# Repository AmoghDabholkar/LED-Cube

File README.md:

# LED-Cube
In this project, we made a 10x10x10 LEDs (2 meters x 2 meters x 2 meters) LED Cube. A LED cube is a visual treat with 3D effects and patterns. It works on the concept of Persistence of Vision.

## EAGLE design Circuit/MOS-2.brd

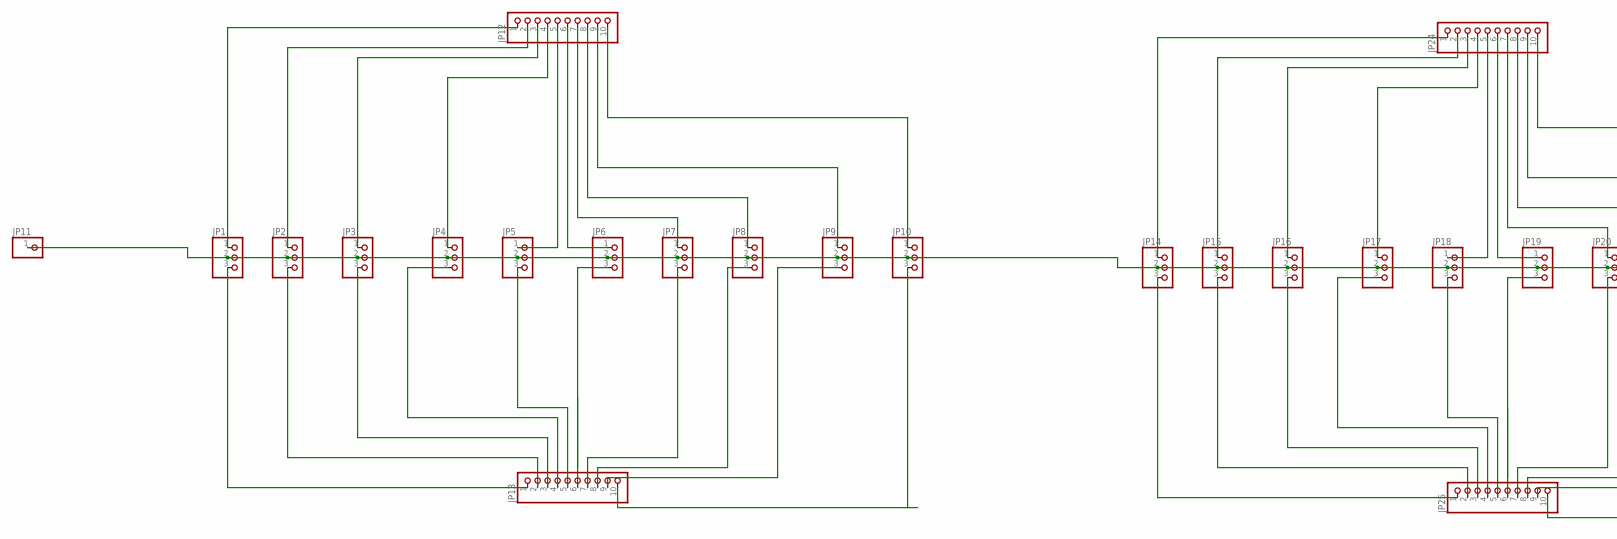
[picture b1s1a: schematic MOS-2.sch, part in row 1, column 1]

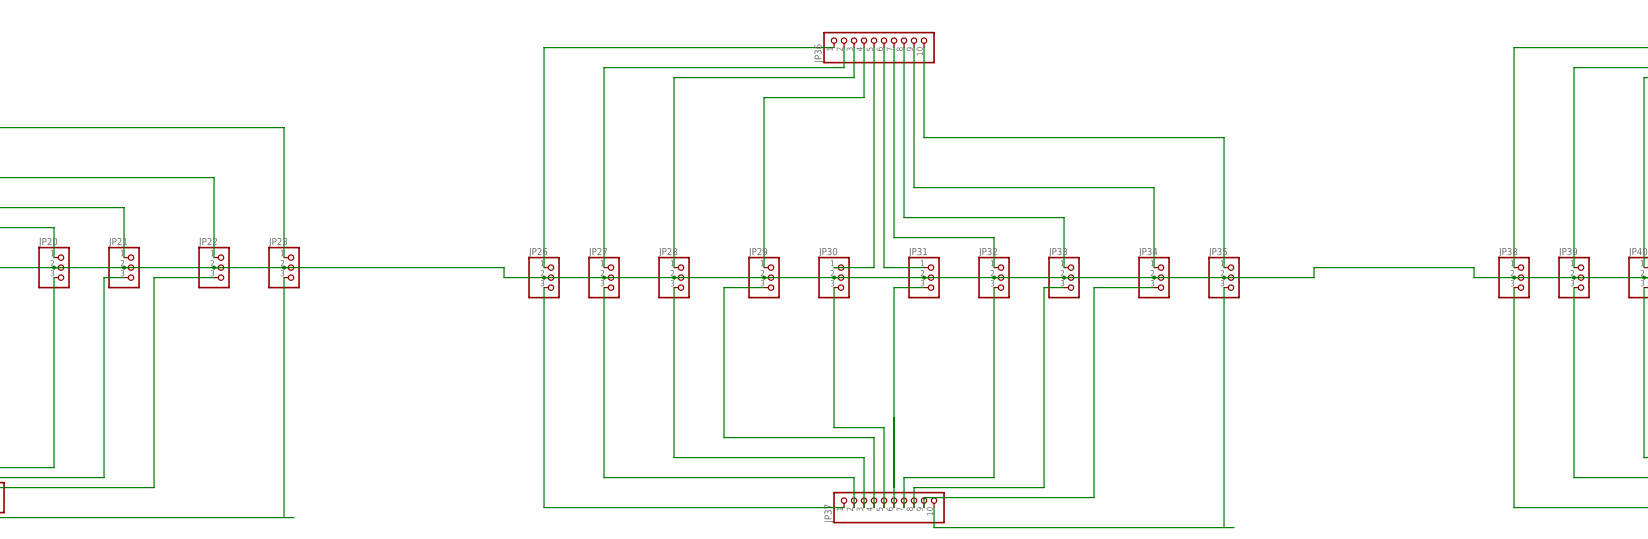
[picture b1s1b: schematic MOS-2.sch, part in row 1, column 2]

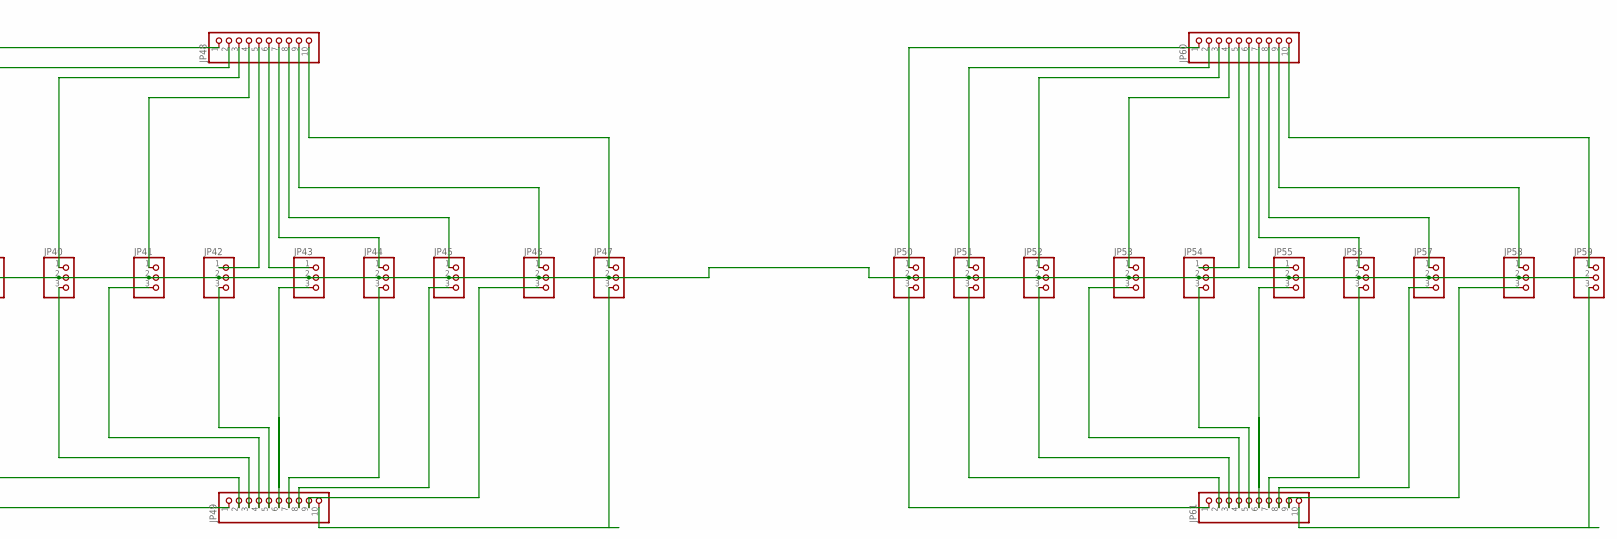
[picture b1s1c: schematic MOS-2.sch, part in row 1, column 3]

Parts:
JP1, JP2, JP3, JP4, JP5, JP6, JP7, JP8, JP9, JP10, JP14, JP15, JP16, JP17, JP18, JP19, JP20, JP21, JP22, JP23, JP26, JP27, JP28, JP29, JP30, JP31, JP32, JP33, JP34, JP35, JP38, JP39, JP40, JP41, JP42, JP43, JP44, JP45, JP46, JP47, JP50, JP51, JP52, JP53, JP54, JP55, JP56, JP57, JP58, JP59: PINHD-1X3; 1X03
JP11: PINHD-1X1; 1X01
JP12, JP13, JP24, JP25, JP36, JP37, JP48, JP49, JP60, JP61: PINHD-1X10; 1X10

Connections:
unnamed: JP1.2, JP2.2, JP3.2, JP4.2, JP5.2, JP6.2, JP7.2, JP8.2, JP9.2, JP10.2, JP11.1, JP14.2, JP15.2, JP16.2, JP17.2, JP18.2, JP19.2, JP20.2, JP21.2, JP22.2, JP23.2, JP26.2, JP27.2, JP28.2, JP29.2, JP30.2, JP31.2, JP32.2, JP33.2, JP34.2, JP35.2, JP38.2, JP39.2, JP40.2, JP41.2, JP42.2, JP43.2, JP44.2, JP45.2, JP46.2, JP47.2, JP50.2, JP51.2, JP52.2, JP53.2, JP54.2, JP55.2, JP56.2, JP57.2, JP58.2, JP59.2
unnamed: JP1.1, JP12.1
unnamed: JP2.1, JP12.2
unnamed: JP3.1, JP12.3
unnamed: JP4.1, JP12.4
unnamed: JP5.1, JP12.5
unnamed: JP6.1, JP12.6
unnamed: JP7.1, JP12.7
unnamed: JP8.1, JP12.8
unnamed: JP9.1, JP12.9
unnamed: JP10.1, JP12.10
unnamed: JP1.3, JP13.1
unnamed: JP2.3, JP13.2
unnamed: JP3.3, JP13.3
unnamed: JP5.3, JP13.5
unnamed: JP10.3, JP13.10
unnamed: JP9.3, JP13.9
unnamed: JP8.3, JP13.8
unnamed: JP7.3, JP13.7
unnamed: JP6.3, JP13.6
unnamed: JP14.1, JP24.1
unnamed: JP4.3, JP13.4
unnamed: JP15.1, JP24.2
unnamed: JP16.1, JP24.3
unnamed: JP17.1, JP24.4
unnamed: JP18.1, JP24.5
unnamed: JP19.1, JP24.6
unnamed: JP20.1, JP24.7
unnamed: JP21.1, JP24.8
unnamed: JP22.1, JP24.9
unnamed: JP23.1, JP24.10
unnamed: JP14.3, JP25.1
unnamed: JP15.3, JP25.2
unnamed: JP16.3, JP25.3
unnamed: JP18.3, JP25.5
unnamed: JP23.3, JP25.10
unnamed: JP22.3, JP25.9
unnamed: JP21.3, JP25.8
unnamed: JP20.3, JP25.7
unnamed: JP19.3, JP25.6
unnamed: JP17.3, JP25.4
unnamed: JP26.1, JP36.1
unnamed: JP27.1, JP36.2
unnamed: JP28.1, JP36.3
unnamed: JP29.1, JP36.4
unnamed: JP30.1, JP36.5
unnamed: JP31.1, JP36.6
unnamed: JP32.1, JP36.7
unnamed: JP33.1, JP36.8
unnamed: JP34.1, JP36.9
unnamed: JP35.1, JP36.10
unnamed: JP26.3, JP37.1
unnamed: JP27.3, JP37.2
unnamed: JP28.3, JP37.3
unnamed: JP30.3, JP37.5
unnamed: JP35.3, JP37.10
unnamed: JP34.3, JP37.9
unnamed: JP33.3, JP37.8
unnamed: JP32.3, JP37.7
unnamed: JP31.3, JP37.6
unnamed: JP29.3, JP37.4
unnamed: JP38.1, JP48.1
unnamed: JP39.1, JP48.2
unnamed: JP40.1, JP48.3
unnamed: JP41.1, JP48.4
unnamed: JP42.1, JP48.5
unnamed: JP43.1, JP48.6
unnamed: JP44.1, JP48.7
unnamed: JP45.1, JP48.8
unnamed: JP46.1, JP48.9
unnamed: JP47.1, JP48.10
unnamed: JP38.3, JP49.1
unnamed: JP39.3, JP49.2
unnamed: JP40.3, JP49.3
unnamed: JP42.3, JP49.5
unnamed: JP47.3, JP49.10
unnamed: JP46.3, JP49.9
unnamed: JP45.3, JP49.8
unnamed: JP44.3, JP49.7
unnamed: JP43.3, JP49.6
unnamed: JP41.3, JP49.4
unnamed: JP50.1, JP60.1
unnamed: JP51.1, JP60.2
unnamed: JP52.1, JP60.3
unnamed: JP53.1, JP60.4
unnamed: JP54.1, JP60.5
unnamed: JP55.1, JP60.6
unnamed: JP56.1, JP60.7
unnamed: JP57.1, JP60.8
unnamed: JP58.1, JP60.9
unnamed: JP59.1, JP60.10
unnamed: JP50.3, JP61.1
unnamed: JP51.3, JP61.2
unnamed: JP52.3, JP61.3
unnamed: JP54.3, JP61.5
unnamed: JP59.3, JP61.10
unnamed: JP58.3, JP61.9
unnamed: JP57.3, JP61.8
unnamed: JP56.3, JP61.7
unnamed: JP55.3, JP61.6
unnamed: JP53.3, JP61.4

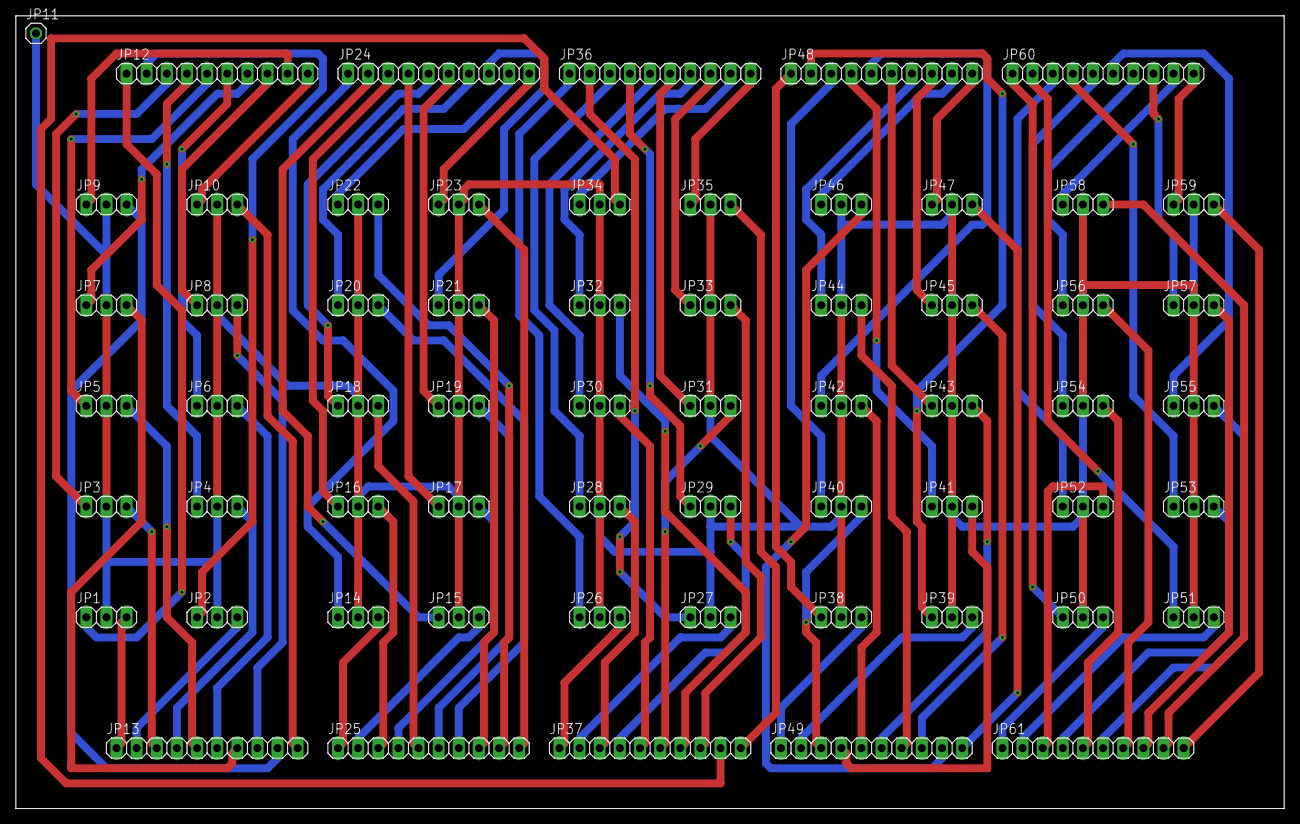
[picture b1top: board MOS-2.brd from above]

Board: 2 copper layers, 160.0 x 100.0 mm, 61 parts (0 on the bottom side), 101 nets.

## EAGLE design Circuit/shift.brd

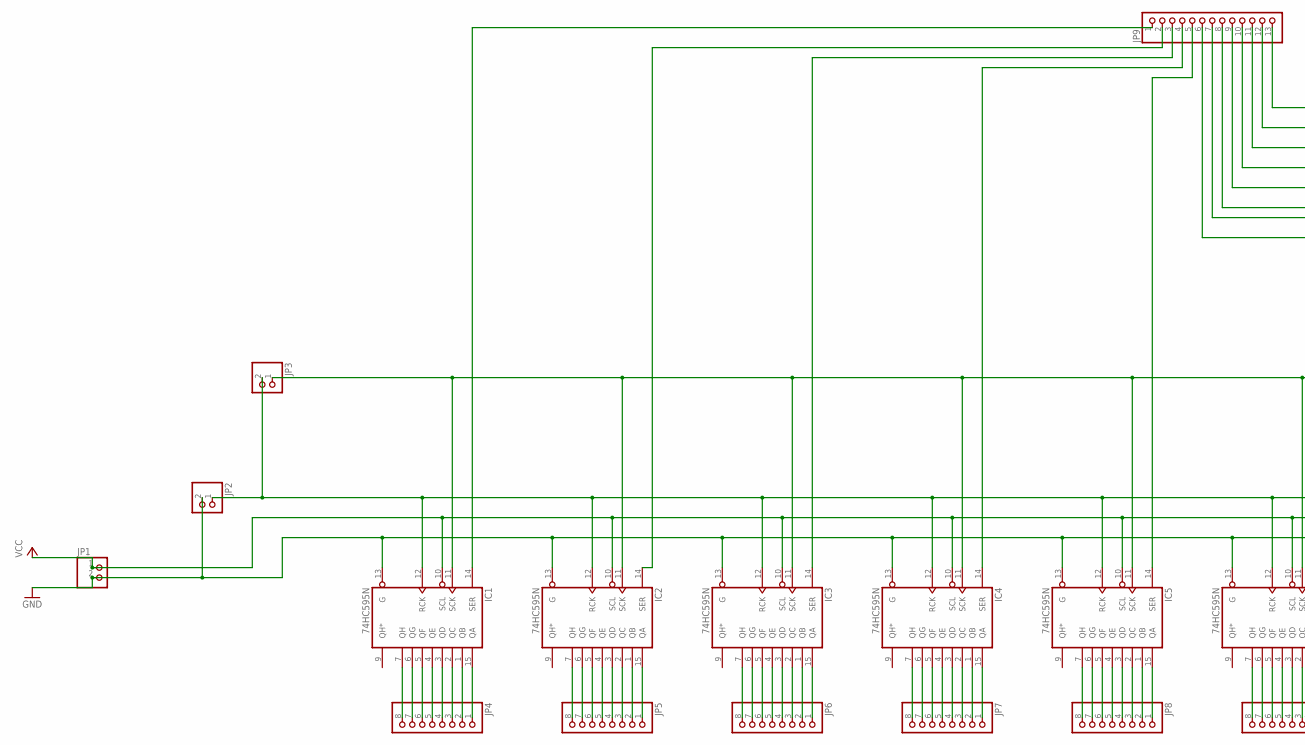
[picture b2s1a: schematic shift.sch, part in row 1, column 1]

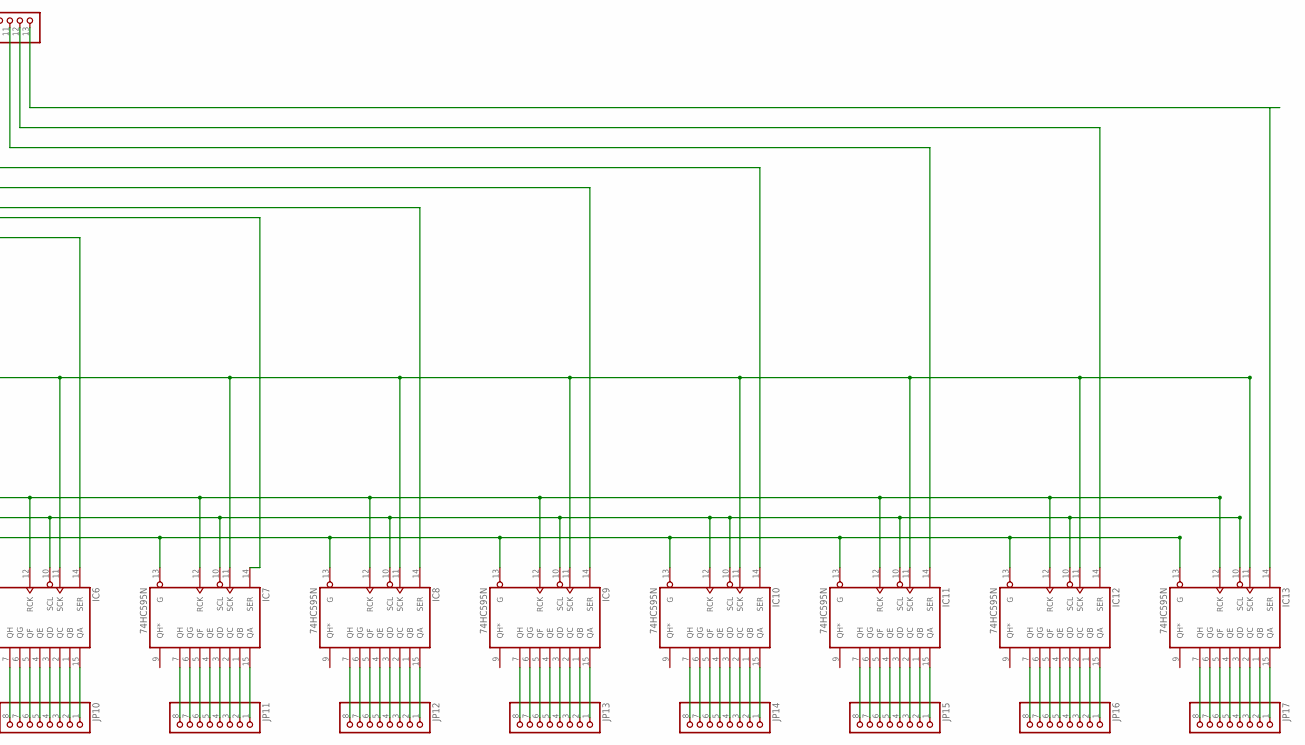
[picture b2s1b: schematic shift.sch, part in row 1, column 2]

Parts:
IC1, IC2, IC3, IC4, IC5, IC6, IC7, IC8, IC9, IC10, IC11, IC12, IC13: 74HC595N; DIL16
JP1, JP2, JP3: PINHD-1X2; 1X02
JP4, JP5, JP6, JP7, JP8, JP10, JP11, JP12, JP13, JP14, JP15, JP16, JP17: PINHD-1X8; 1X08
JP9: PINHD-1X13; 1X13

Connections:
GND: IC1.8 (GND), IC1.13 (G), IC2.8 (GND), IC2.13 (G), IC3.8 (GND), IC3.13 (G), IC4.8 (GND), IC4.13 (G), IC5.8 (GND), IC5.13 (G), IC6.8 (GND), IC6.13 (G), IC7.8 (GND), IC7.13 (G), IC8.8 (GND), IC8.13 (G), IC9.8 (GND), IC9.13 (G), IC10.8 (GND), IC10.13 (G), IC11.8 (GND), IC11.13 (G), IC12.8 (GND), IC12.13 (G), IC13.8 (GND), IC13.13 (G), JP1.2, JP2.2
unnamed: IC1.7 (QH), JP4.8
unnamed: IC1.6 (QG), JP4.7
unnamed: IC1.5 (QF), JP4.6
unnamed: IC1.4 (QE), JP4.5
unnamed: IC1.3 (QD), JP4.4
unnamed: IC1.2 (QC), JP4.3
unnamed: IC1.1 (QB), JP4.2
unnamed: IC1.15 (QA), JP4.1
unnamed: IC1.11 (SCK), IC2.11 (SCK), IC3.11 (SCK), IC4.11 (SCK), IC5.11 (SCK), IC6.11 (SCK), IC7.11 (SCK), IC8.11 (SCK), IC9.11 (SCK), IC10.11 (SCK), IC11.11 (SCK), IC12.11 (SCK), IC13.11 (SCK), JP3.1
unnamed: IC1.14 (SER), JP9.1
unnamed: IC2.14 (SER), JP9.2
unnamed: IC2.7 (QH), JP5.8
unnamed: IC2.6 (QG), JP5.7
unnamed: IC2.5 (QF), JP5.6
unnamed: IC2.4 (QE), JP5.5
unnamed: IC2.3 (QD), JP5.4
unnamed: IC2.2 (QC), JP5.3
unnamed: IC2.1 (QB), JP5.2
unnamed: IC2.15 (QA), JP5.1
unnamed: IC3.14 (SER), JP9.3
unnamed: IC4.14 (SER), JP9.4
unnamed: IC3.7 (QH), JP6.8
unnamed: IC3.6 (QG), JP6.7
unnamed: IC3.5 (QF), JP6.6
unnamed: IC3.4 (QE), JP6.5
unnamed: IC3.3 (QD), JP6.4
unnamed: IC3.2 (QC), JP6.3
unnamed: IC3.1 (QB), JP6.2
unnamed: IC3.15 (QA), JP6.1
unnamed: IC5.14 (SER), JP9.5
unnamed: IC6.7 (QH), JP10.8
unnamed: IC4.7 (QH), JP7.8
unnamed: IC4.6 (QG), JP7.7
unnamed: IC4.5 (QF), JP7.6
unnamed: IC4.4 (QE), JP7.5
unnamed: IC4.3 (QD), JP7.4
unnamed: IC4.2 (QC), JP7.3
unnamed: IC4.1 (QB), JP7.2
unnamed: IC4.15 (QA), JP7.1
unnamed: IC6.6 (QG), JP10.7
unnamed: IC6.5 (QF), JP10.6
unnamed: IC5.7 (QH), JP8.8
unnamed: IC5.6 (QG), JP8.7
unnamed: IC5.5 (QF), JP8.6
unnamed: IC5.4 (QE), JP8.5
unnamed: IC5.3 (QD), JP8.4
unnamed: IC5.2 (QC), JP8.3
unnamed: IC5.1 (QB), JP8.2
unnamed: IC5.15 (QA), JP8.1
unnamed: IC6.4 (QE), JP10.5
unnamed: IC6.3 (QD), JP10.4
unnamed: IC6.2 (QC), JP10.3
unnamed: IC6.1 (QB), JP10.2
unnamed: IC6.15 (QA), JP10.1
unnamed: IC7.7 (QH), JP11.8
unnamed: IC7.6 (QG), JP11.7
unnamed: IC7.5 (QF), JP11.6
unnamed: IC7.4 (QE), JP11.5
unnamed: IC7.3 (QD), JP11.4
unnamed: IC7.2 (QC), JP11.3
unnamed: IC7.1 (QB), JP11.2
unnamed: IC7.15 (QA), JP11.1
unnamed: IC8.7 (QH), JP12.8
unnamed: IC8.6 (QG), JP12.7
unnamed: IC8.5 (QF), JP12.6
unnamed: IC8.4 (QE), JP12.5
unnamed: IC8.3 (QD), JP12.4
unnamed: IC8.2 (QC), JP12.3
unnamed: IC8.1 (QB), JP12.2
unnamed: IC8.15 (QA), JP12.1
unnamed: IC9.7 (QH), JP13.8
unnamed: IC9.6 (QG), JP13.7
unnamed: IC9.5 (QF), JP13.6
unnamed: IC9.4 (QE), JP13.5
unnamed: IC9.3 (QD), JP13.4
unnamed: IC9.2 (QC), JP13.3
unnamed: IC9.1 (QB), JP13.2
unnamed: IC9.15 (QA), JP13.1
unnamed: IC10.7 (QH), JP14.8
unnamed: IC10.6 (QG), JP14.7
unnamed: IC10.5 (QF), JP14.6
unnamed: IC10.4 (QE), JP14.5
unnamed: IC10.3 (QD), JP14.4
unnamed: IC10.2 (QC), JP14.3
unnamed: IC10.1 (QB), JP14.2
unnamed: IC10.15 (QA), JP14.1
unnamed: IC6.14 (SER), JP9.6
unnamed: IC7.14 (SER), JP9.7
unnamed: IC8.14 (SER), JP9.8
unnamed: IC9.14 (SER), JP9.9
unnamed: IC10.14 (SER), JP9.10
unnamed: IC11.7 (QH), JP15.8
unnamed: IC11.6 (QG), JP15.7
unnamed: IC11.5 (QF), JP15.6
unnamed: IC11.4 (QE), JP15.5
unnamed: IC11.3 (QD), JP15.4
unnamed: IC11.2 (QC), JP15.3
unnamed: IC11.1 (QB), JP15.2
unnamed: IC11.15 (QA), JP15.1
unnamed: IC12.7 (QH), JP16.8
unnamed: IC12.6 (QG), JP16.7
unnamed: IC12.5 (QF), JP16.6
unnamed: IC12.4 (QE), JP16.5
unnamed: IC12.3 (QD), JP16.4
unnamed: IC12.2 (QC), JP16.3
unnamed: IC12.1 (QB), JP16.2
unnamed: IC12.15 (QA), JP16.1
unnamed: IC13.7 (QH), JP17.8
unnamed: IC13.6 (QG), JP17.7
unnamed: IC13.5 (QF), JP17.6
unnamed: IC13.4 (QE), JP17.5
unnamed: IC13.3 (QD), JP17.4
unnamed: IC13.2 (QC), JP17.3
unnamed: IC13.1 (QB), JP17.2
unnamed: IC13.15 (QA), JP17.1
unnamed: IC11.14 (SER), JP9.11
unnamed: IC12.14 (SER), JP9.12
unnamed: IC13.14 (SER), JP9.13
unnamed: IC1.12 (RCK), IC2.12 (RCK), IC3.12 (RCK), IC4.12 (RCK), IC5.12 (RCK), IC6.12 (RCK), IC7.12 (RCK), IC8.12 (RCK), IC9.12 (RCK), IC11.12 (RCK), IC12.12 (RCK), IC13.12 (RCK), JP2.1, JP3.2
VCC: IC1.10 (SCL), IC1.16 (VCC), IC2.10 (SCL), IC2.16 (VCC), IC3.10 (SCL), IC3.16 (VCC), IC4.10 (SCL), IC4.16 (VCC), IC5.10 (SCL), IC5.16 (VCC), IC6.10 (SCL), IC6.16 (VCC), IC7.10 (SCL), IC7.16 (VCC), IC8.10 (SCL), IC8.16 (VCC), IC9.10 (SCL), IC9.16 (VCC), IC10.10 (SCL), IC10.12 (RCK), IC10.16 (VCC), IC11.10 (SCL), IC11.16 (VCC), IC12.10 (SCL), IC12.16 (VCC), IC13.10 (SCL), IC13.16 (VCC), JP1.1

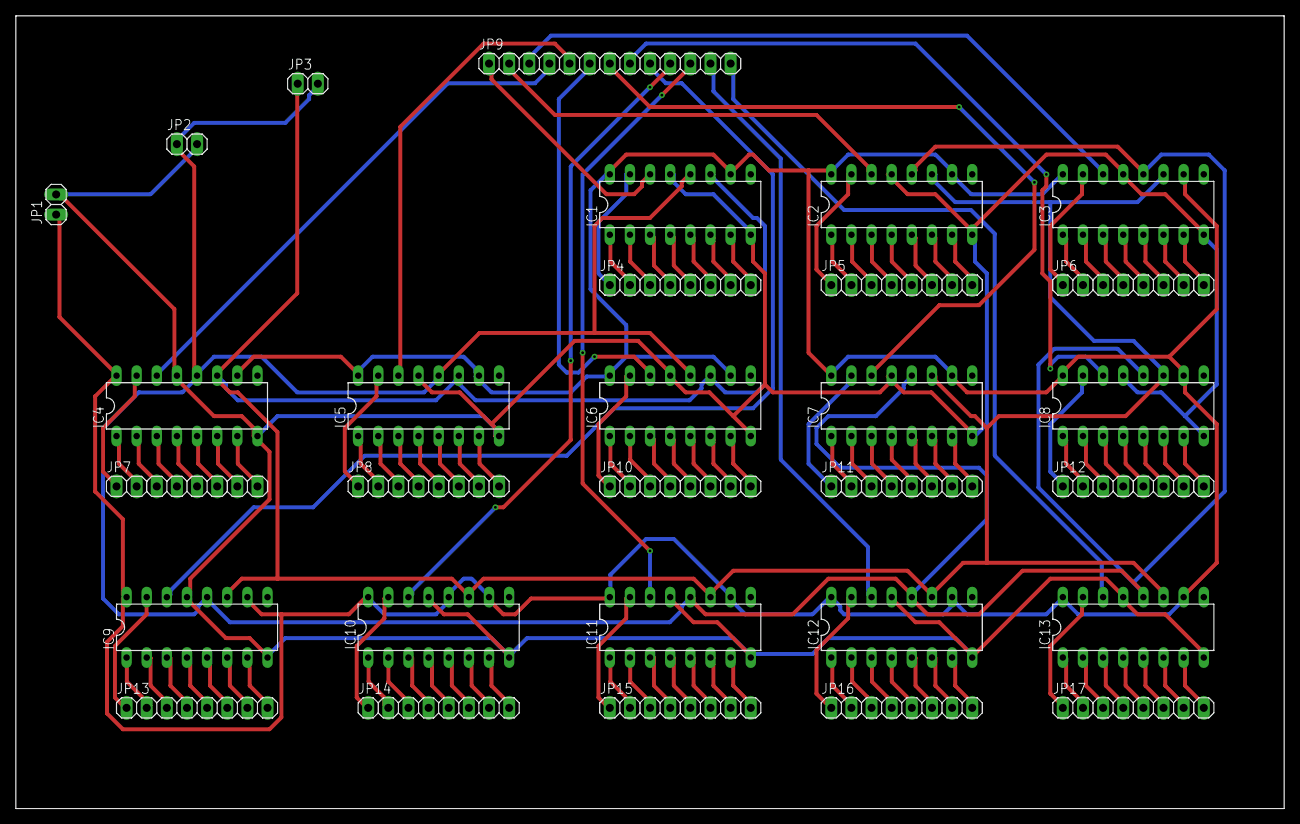
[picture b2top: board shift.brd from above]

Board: 2 copper layers, 160.0 x 100.0 mm, 30 parts (0 on the bottom side), 121 nets.

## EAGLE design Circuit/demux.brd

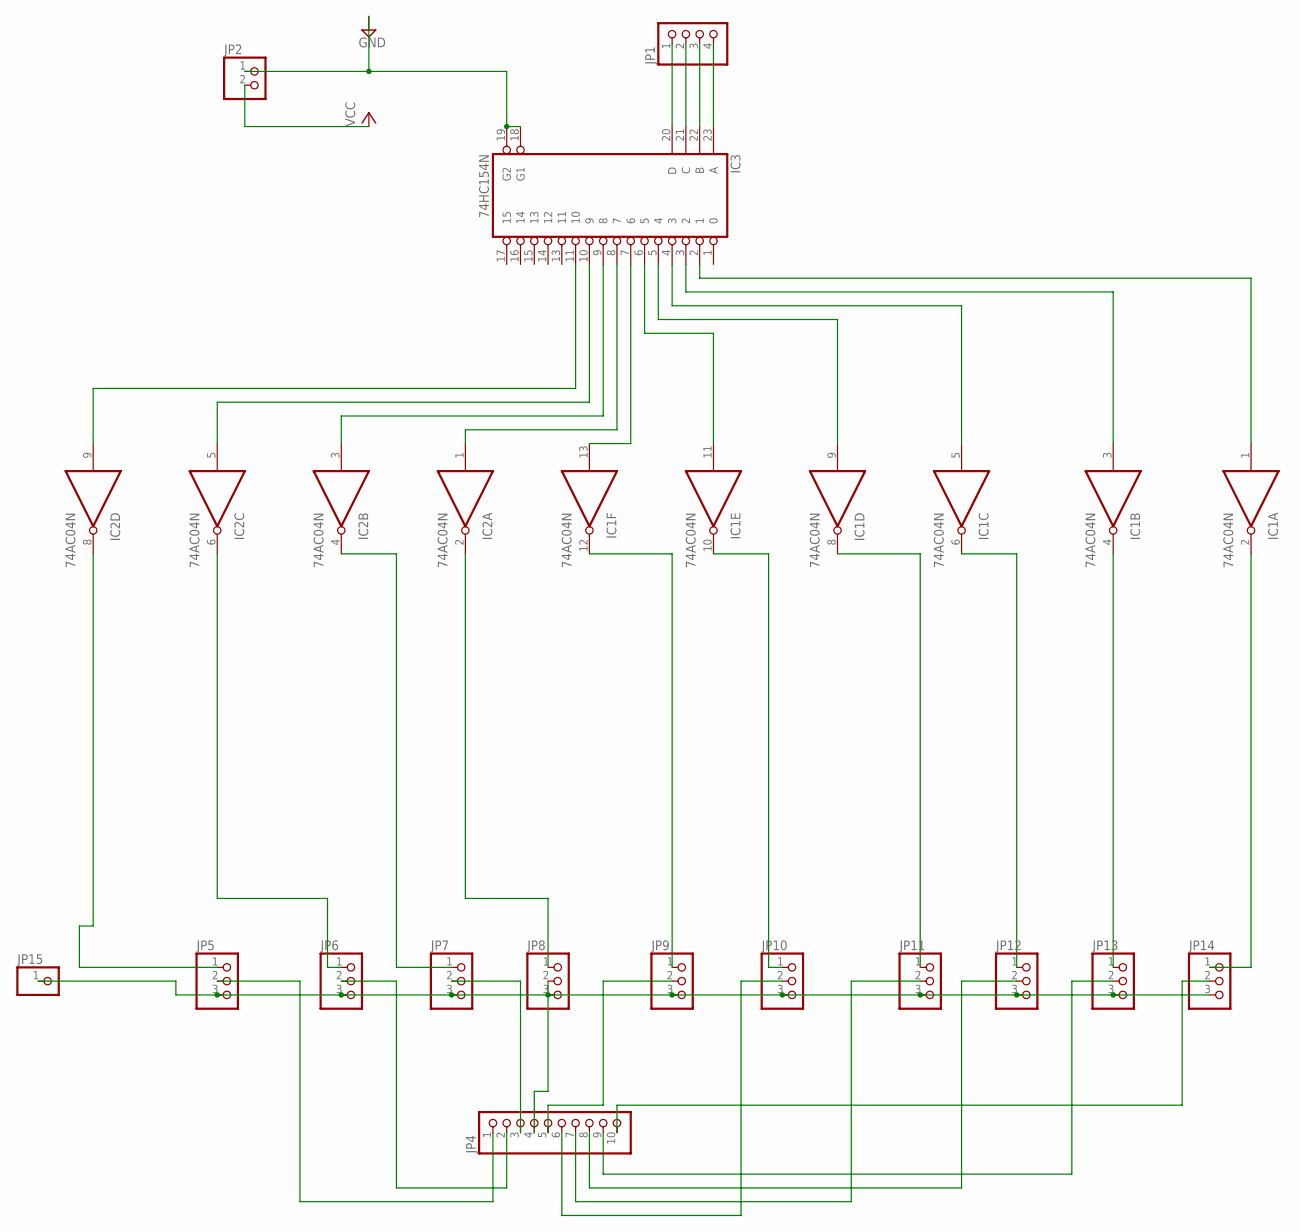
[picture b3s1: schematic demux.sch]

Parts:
IC1, IC2: 74AC04N; DIL14
IC3: 74HC154N; DIL24-6
JP1: PINHD-1X4; 1X04
JP2: PINHD-1X2; 1X02
JP4: PINHD-1X10; 1X10
JP5, JP6, JP7, JP8, JP9, JP10, JP11, JP12, JP13, JP14: PINHD-1X3; 1X03
JP15: PINHD-1X1; 1X01

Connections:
GND: IC1.7 (GND), IC2.7 (GND), IC3.12 (GND), IC3.18 (G1), IC3.19 (G2), JP2.1
unnamed: IC3.20 (D), JP1.1
unnamed: IC3.21 (C), JP1.2
unnamed: IC3.22 (B), JP1.3
unnamed: IC3.23 (A), JP1.4
unnamed: IC1.1 (I), IC3.2 (1)
unnamed: IC1.3 (I), IC3.3 (2)
unnamed: IC1.5 (I), IC3.4 (3)
unnamed: IC1.9 (I), IC3.5 (4)
unnamed: IC1.11 (I), IC3.6 (5)
unnamed: IC1.13 (I), IC3.7 (6)
unnamed: IC2.1 (I), IC3.8 (7)
unnamed: IC2.3 (I), IC3.9 (8)
unnamed: IC2.5 (I), IC3.10 (9)
unnamed: IC2.9 (I), IC3.11 (10)
unnamed: IC2.8 (O), JP5.1
unnamed: IC2.4 (O), JP7.1
unnamed: IC2.2 (O), JP8.1
unnamed: IC1.12 (O), JP9.1
unnamed: IC1.8 (O), JP11.1
unnamed: IC1.6 (O), JP12.1
unnamed: IC1.4 (O), JP13.1
unnamed: IC1.2 (O), JP14.1
unnamed: JP5.3, JP6.3, JP7.3, JP8.3, JP9.3, JP10.3, JP11.3, JP12.3, JP13.3, JP14.3, JP15.1
unnamed: IC2.6 (O), JP6.1
unnamed: IC1.10 (O), JP10.1
unnamed: JP4.1, JP5.2
unnamed: JP4.2, JP6.2
unnamed: JP4.3, JP7.2
unnamed: JP4.4, JP8.2
unnamed: JP4.5, JP9.2
unnamed: JP4.6, JP10.2
unnamed: JP4.7, JP11.2
unnamed: JP4.8, JP12.2
unnamed: JP4.9, JP13.2
unnamed: JP4.10, JP14.2
VCC: IC1.14 (VCC), IC2.14 (VCC), IC3.24 (VCC), JP2.2

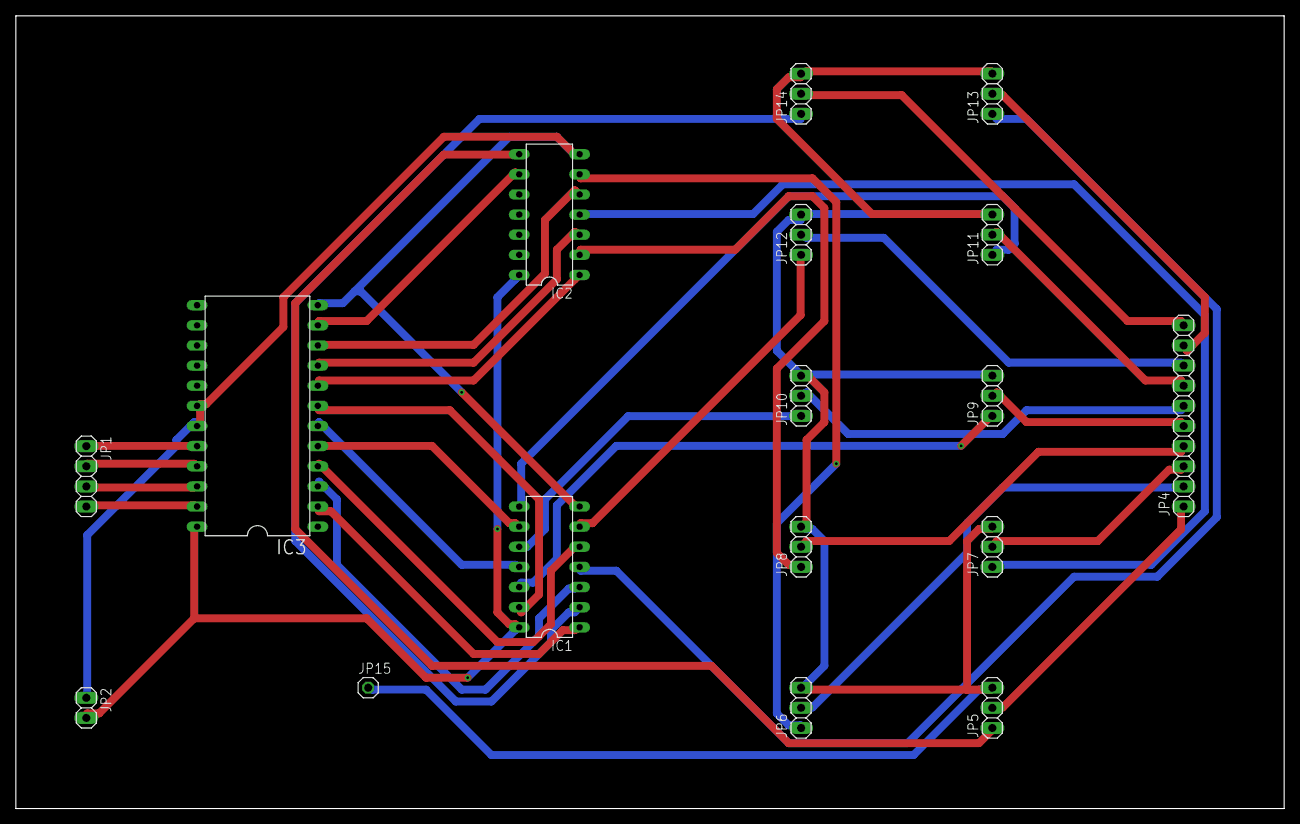
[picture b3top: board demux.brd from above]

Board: 2 copper layers, 160.0 x 100.0 mm, 17 parts (0 on the bottom side), 37 nets.

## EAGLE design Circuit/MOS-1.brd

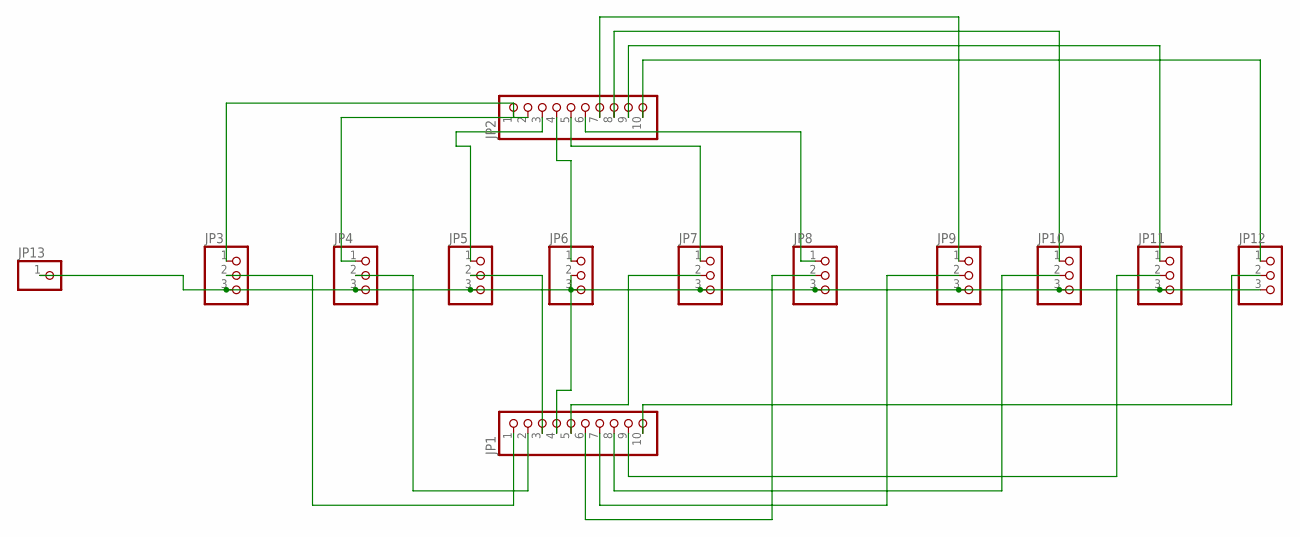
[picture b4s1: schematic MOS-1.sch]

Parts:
JP1, JP2: PINHD-1X10; 1X10
JP3, JP4, JP5, JP6, JP7, JP8, JP9, JP10, JP11, JP12: PINHD-1X3; 1X03
JP13: PINHD-1X1; 1X01

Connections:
unnamed: JP3.3, JP4.3, JP5.3, JP6.3, JP7.3, JP8.3, JP9.3, JP10.3, JP11.3, JP12.3, JP13.1
unnamed: JP2.1, JP3.1
unnamed: JP2.2, JP4.1
unnamed: JP2.3, JP5.1
unnamed: JP2.4, JP6.1
unnamed: JP2.5, JP7.1
unnamed: JP2.6, JP8.1
unnamed: JP2.7, JP9.1
unnamed: JP2.8, JP10.1
unnamed: JP2.9, JP11.1
unnamed: JP2.10, JP12.1
unnamed: JP1.1, JP3.2
unnamed: JP1.2, JP4.2
unnamed: JP1.3, JP5.2
unnamed: JP1.4, JP6.2
unnamed: JP1.5, JP7.2
unnamed: JP1.6, JP8.2
unnamed: JP1.7, JP9.2
unnamed: JP1.8, JP10.2
unnamed: JP1.9, JP11.2
unnamed: JP1.10, JP12.2

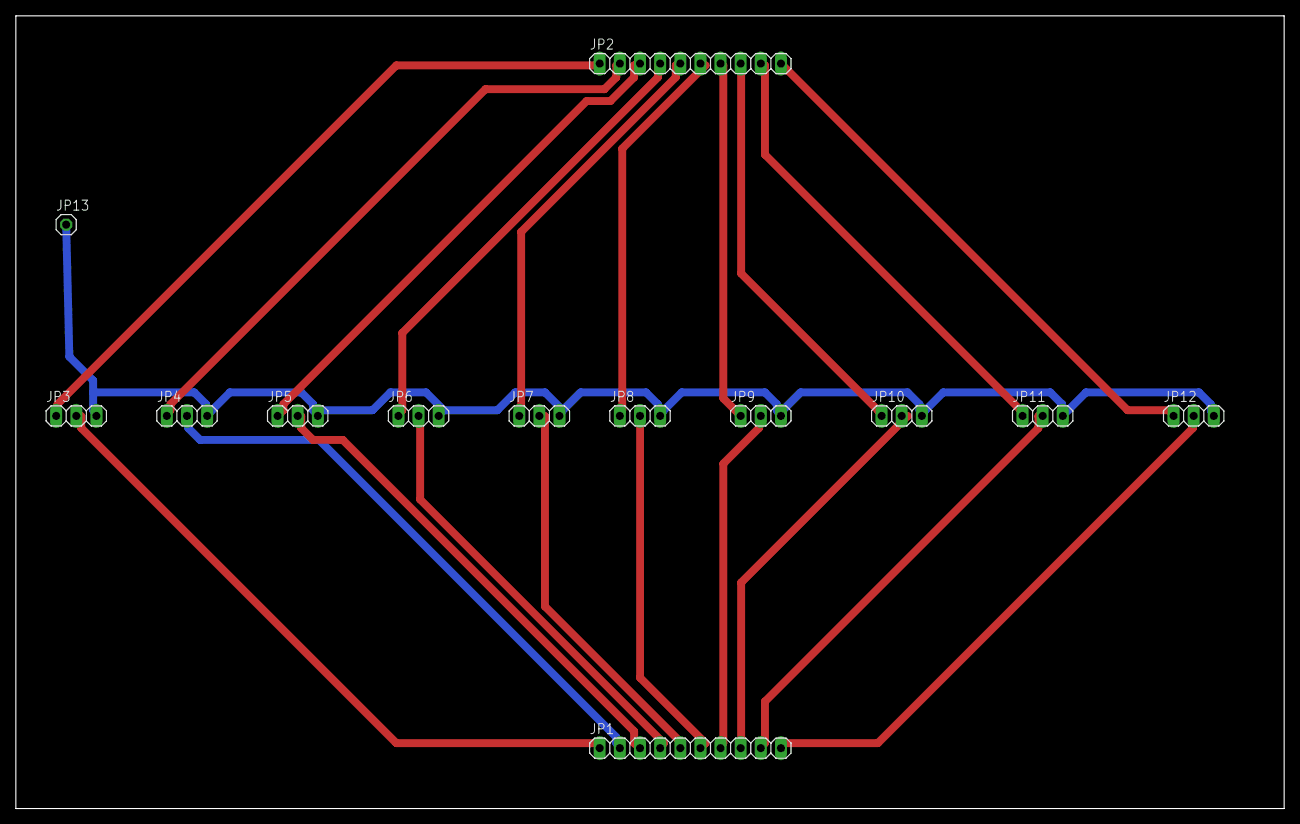
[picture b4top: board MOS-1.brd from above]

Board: 2 copper layers, 160.0 x 100.0 mm, 13 parts (0 on the bottom side), 21 nets.

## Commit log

2019-01-10 Create code
